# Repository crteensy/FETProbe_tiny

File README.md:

# FETProbe_tiny

A tiny 1.3 GHz FET Probe. 

You can find [measurements here](https://electronicprojectsforfun.wordpress.com/solder-in-probes/). Additional details on the design of this probe [can be found on Hackaday](https://hackaday.io/project/184924-diy-13-ghz-fet-probe).

## Stackup

Any standard 1.6 mm thickness stackup should do the job. 1.6 mm is relevant here because it has an influence on the input capacitance.

## Production files

You can find production files under the "Summary" -> "Artifacts" section of the "Actions" tab, or in the releases section.

Manufacturing files are automatically generated for JLCPCB and included in `manufacturing.zip`. Additional documents can be found in `assembly and debugging.zip`.

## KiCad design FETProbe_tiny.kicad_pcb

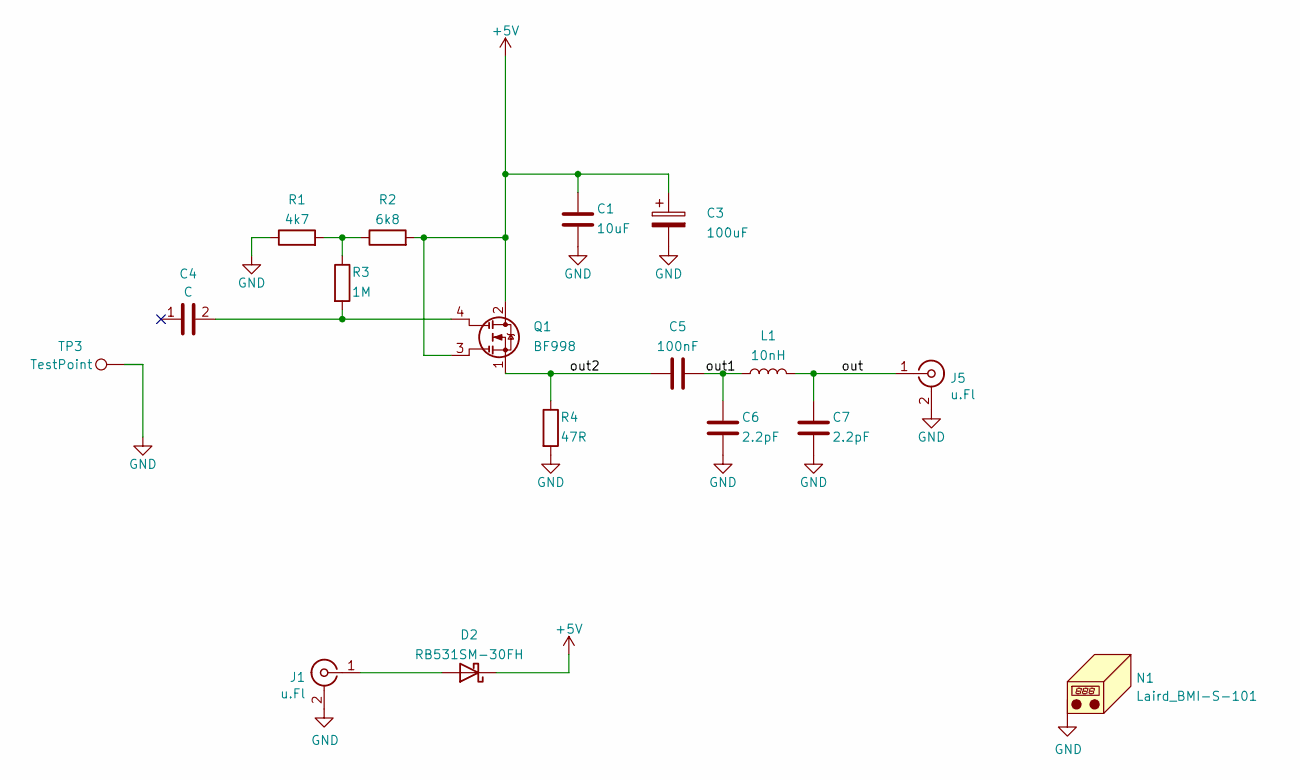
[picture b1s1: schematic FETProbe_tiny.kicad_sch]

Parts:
C1: 10uF; C_0402_1005Metric; voltage 10V; LCSC C15525
C3: 100uF; CP_EIA-3216-18_Kemet-A; voltage 6V3; LCSC C122251
C4: C; input_cap
C5: 100nF; C_1206_3216Metric; LCSC C97946
C6, C7: 2.2pF; C_0402_1005Metric; LCSC C437438
D2: RB531SM-30FH; D_SOD-523; LCSC C50676
J1, J5: u.Fl; U.FL_Molex_MCRF_73412-0110_Vertical; LCSC C88374
L1: 10nH; L_0402_1005Metric; LCSC C382409
N1: Laird_BMI-S-101; Laird_Technologies_BMI-S-101_13.66x12.70mm
Q1: BF998; SOT-143_mod; LCSC C108141
R1: 4k7; R_0402_1005Metric; LCSC C25900
R2: 6k8; R_0402_1005Metric; LCSC C25917
R3: 1M; R_0402_1005Metric; LCSC C26083
R4: 47R; R_0402_1005Metric; LCSC C25118
TP3: TestPoint; TestPoint_THTPad_D2.0mm_Drill1.0mm

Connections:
+5V: C1.2, C3.1, D2.1 (K), Q1.2 (D), Q1.3 (G2), R2.2
/out: C7.2, J5.1 (In), L1.2
/out1: C5.2, C6.2, L1.1
/out2: C5.1, Q1.1 (S), R4.1
GND: C1.1, C3.2, C6.1, C7.1, J1.2 (Ext), J5.2 (Ext), N1.1 (PAD), R1.1, R4.2, TP3.1
unnamed: C4.2, Q1.4 (G1), R3.2
unnamed: D2.2 (A), J1.1 (In)
unnamed: R1.2, R2.1, R3.1

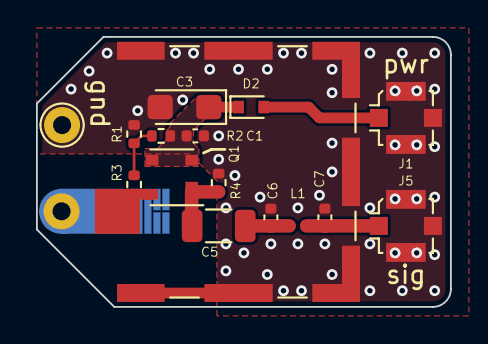
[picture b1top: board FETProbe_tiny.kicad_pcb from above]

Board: 2 copper layers, 23.0 x 15.0 mm, 17 parts (0 on the bottom side), 8 nets.

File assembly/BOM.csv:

Reference;Count;Value;Footprint;Comment;Dielectric;Voltage
    C1;1;10uF;Capacitor_SMD:C_0402_1005Metric;;;10V
    C3;1;100uF;Capacitor_Tantalum_SMD:CP_EIA-3216-18_Kemet-A;;;6V3
    C5;1;100nF;Capacitor_SMD:C_1206_3216Metric;;NP0;
>  C6, C7;2;2.2pF;Capacitor_SMD:C_0402_1005Metric;;NP0;
    D2;1;RB531SM-30FH;Diode_SMD:D_SOD-523;just about any schottky will do;;
>  J1, J5;2;u.Fl;Connector_Coaxial:U.FL_Molex_MCRF_73412-0110_Vertical;;;
    L1;1;10nH;Inductor_SMD:L_0402_1005Metric;;;
    N1;1;Laird_BMI-S-101;RF_Shielding:Laird_Technologies_BMI-S-101_13.66x12.70mm;remove one sidewall;;
    Q1;1;BF998;FETProbe:SOT-143_mod;;;
    R1;1;4k7;Resistor_SMD:R_0402_1005Metric;general purpose;1%;
    R2;1;6k8;Resistor_SMD:R_0402_1005Metric;general purpose;1%;
    R3;1;1M;Resistor_SMD:R_0402_1005Metric;general purpose;1%;
    R4;1;47R;Resistor_SMD:R_0402_1005Metric;general purpose;1%;

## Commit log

2022-04-19 add schematic pdf
2022-04-20 updated gerbers and assembly info
2022-04-20 minor: update component properties in layout
2022-07-30 Add gitignore
2022-07-30 Add LCSC numbers
2022-07-30 Add kibot
2022-07-30 Remove grid origin marker
    It confuses JLCPCB assembly
